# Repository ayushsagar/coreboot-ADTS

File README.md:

coreboot-ADTS
=============

Automated Distributed Test System for coreboot: A Google Summer of Code 2013 project at coreboot.
Original proposal: http://www.google-melange.com/gsoc/project/details/google/gsoc2013/ayush3504/5665319561461760

Please see documentation to see how it is implemented:
https://github.com/ayushsagar/coreboot-ADTS/blob/master/Documentation/test%20interfaces%20for%20CADTS.pdf

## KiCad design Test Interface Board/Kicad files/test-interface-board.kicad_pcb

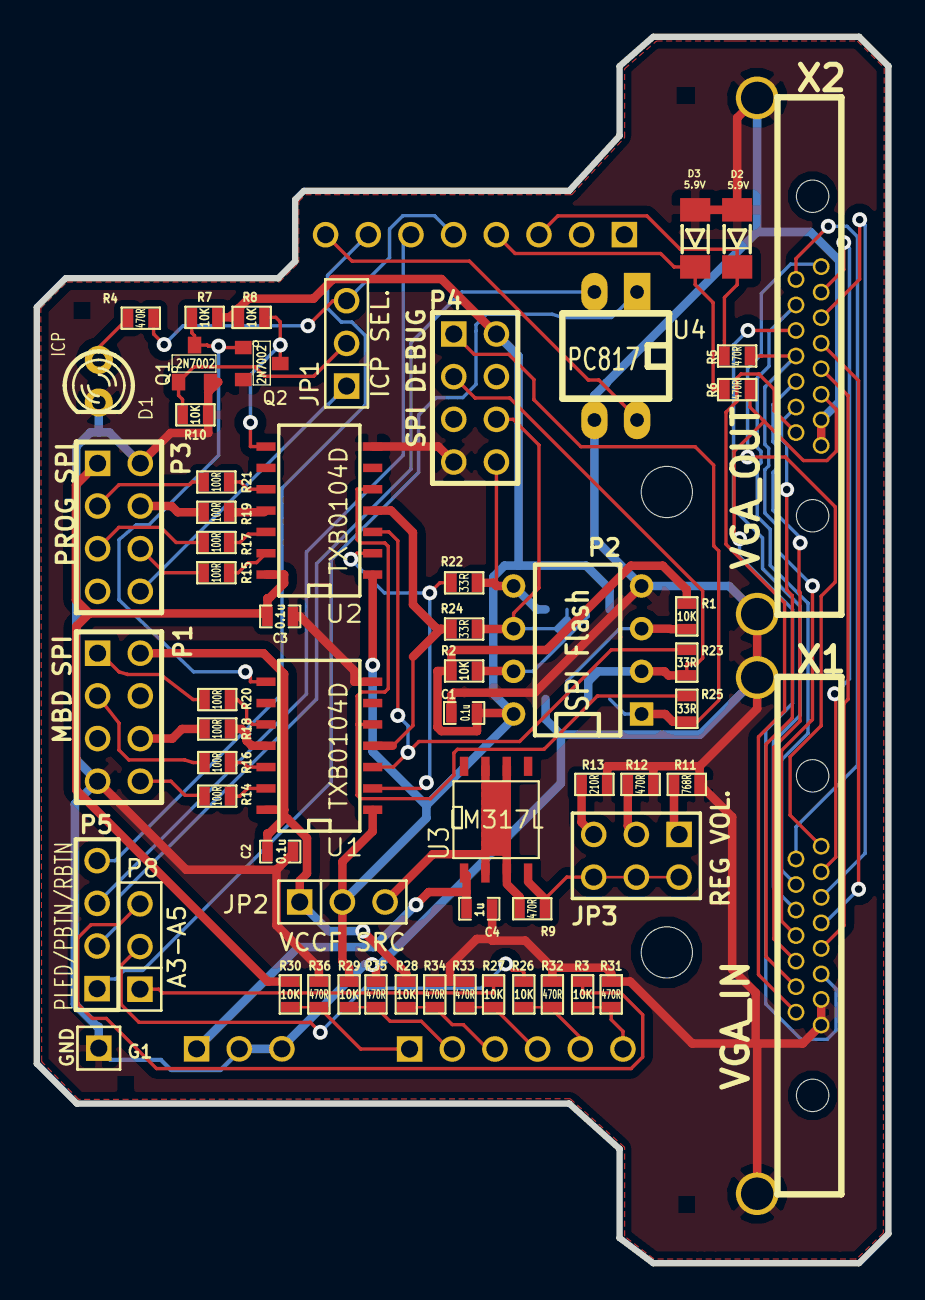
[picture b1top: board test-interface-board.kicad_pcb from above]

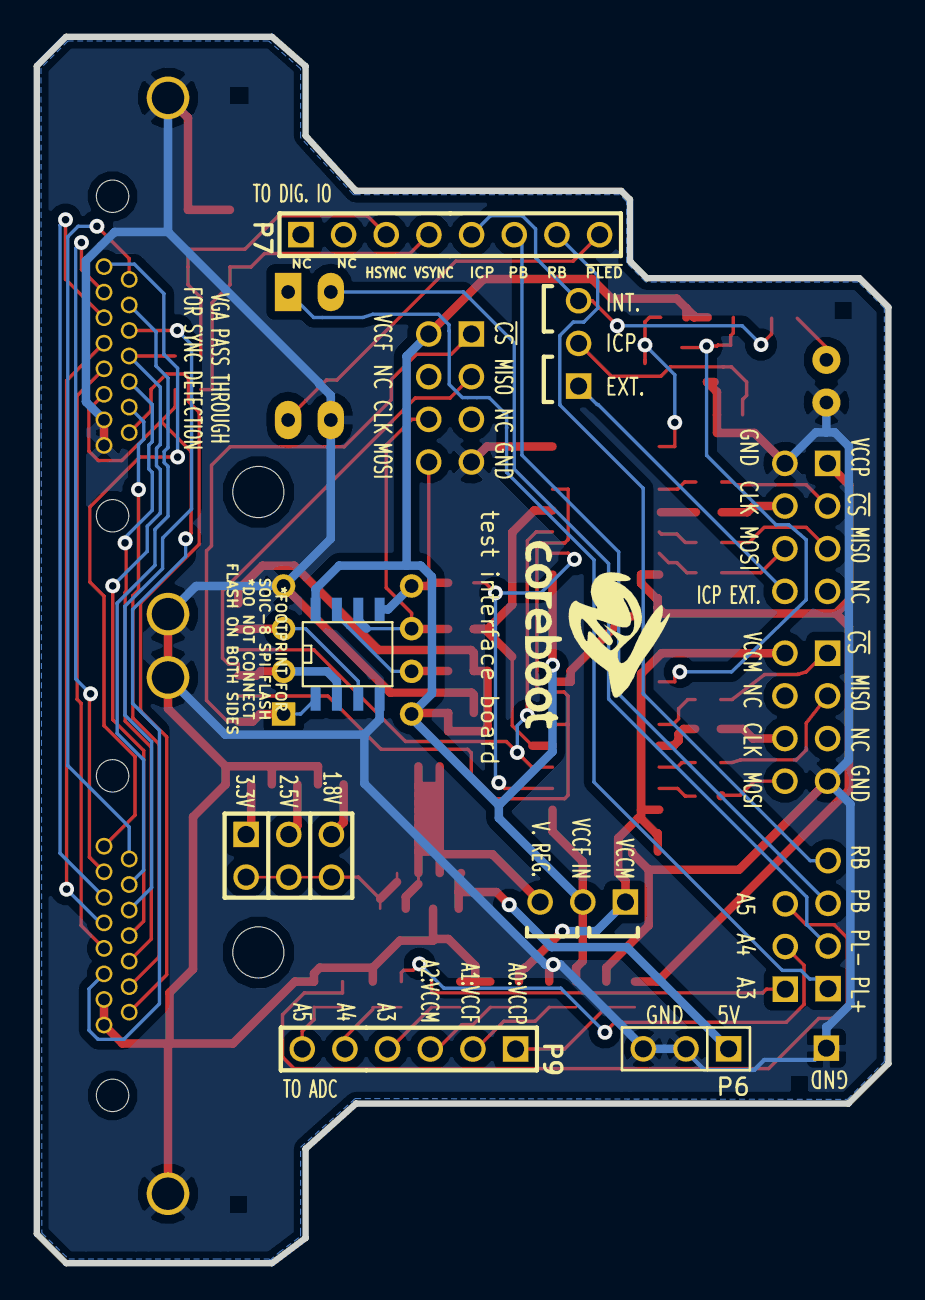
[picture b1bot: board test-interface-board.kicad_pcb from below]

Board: 2 copper layers, 50.7 x 73.0 mm, 67 parts (4 on the bottom side), 71 nets.

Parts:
C1, C2, C3: 0.1u; SM0603_Capa
C4: 1u; SM0603_Capa
D1: ICP; LED-3MM
D2, D3: 5.9V; MiniMelf
G1: GND; PIN_ARRAY_1
JP1: ICP SEL.; PIN_ARRAY_3X1
JP2: VCCF SRC; PIN_ARRAY_3X1
JP3: REG VOL.; pin_array_3x2
P1: MBD SPI; pin_array_4x2
P2: SPI Flash; DIP-8__300
P3: PROG SPI; pin_array_4x2
P4: SPI DEBUG; pin_array_4x2
P5: PLED/PBTN/RBTN; PIN_ARRAY_4x1
P6: POWER; PIN_ARRAY_3X1
P7: D0-D7; PIN_ARRAY_8x1
P8: A3-A5; PIN_ARRAY_3X1
P9: A0-A5; PIN_ARRAY_6x1
P10: SPI Flash; SO8E
Q1, Q2: 2N7002; SOT23
R1, R2, R3, R7, R8, R10, R26, R27, R28, R29, R30: 10K; SM0603
R4, R5, R6, R9, R12, R31, R32, R33, R34, R35, R36: 470R; SM0603
R11: 768R; SM0603
R13: 210R; SM0603
R14, R15, R16, R17, R18, R19, R20, R21: 100R; SM0603
R22, R23, R24, R25: 33R; SM0603
U1, U2: TXB0104D; SO14N
U3: LM317L; SO8N
U4: PC817; DIP-4__300_ELL
V3, V4: 1pin
X1: VGA_IN; EDAC 634-015-274-990 D-Sub High Density 15 pin Slim
X2: VGA_OUT; EDAC 634-015-274-990 D-Sub High Density 15 pin Slim

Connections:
+5V: C4.1, P6.1, U3.1
/HSYNC: D2.2, P7.3, R5.2
/ICP_INT: JP1.3, P7.5, R4.2
/ICP_IO3: JP1.1, P3.8
/PBTN: P5.3, P7.6
/RBTN: P5.4, P7.7
/SPI change-over switch/CLK_F: P2.6, P4.6, P10.6, R24.2
/SPI change-over switch/CLK_M: P1.6, R18.2
/SPI change-over switch/CLK_P: P3.4, R19.2
/SPI change-over switch/ICP: Q2.3, R8.2, U2.8
/SPI change-over switch/MISO_F: P2.2, P4.3, P10.2, R23.2
/SPI change-over switch/MISO_M: P1.3, R16.2
/SPI change-over switch/MISO_P: P3.5, R17.2
/SPI change-over switch/MOSI_F: P2.5, P4.8, P10.5, R22.2
/SPI change-over switch/MOSI_M: P1.8, R14.2
/SPI change-over switch/MOSI_P: P3.6, R15.2
/SPI change-over switch/SET_ICP: JP1.2, Q1.1, R10.1
/SPI change-over switch/~CS_F~: P2.1, P4.1, P10.1, R25.2
/SPI change-over switch/~CS_M~: P1.1, R20.2
/SPI change-over switch/~CS_P~: P3.3, R21.2
/SPI change-over switch/~ICP~: Q1.3, Q2.1, R7.2, U1.8
/VP1: X1.1, X2.1
/VP2: X1.2, X2.2
/VP3: X1.3, X2.3
/VP4: X1.4, X2.4
/VP6: X1.6, X2.6
/VP7: X1.7, X2.7
/VP8: X1.8, X2.8
/VP9: X1.9, X2.9
/VP11: X1.11, X2.11
/VP12: X1.12, X2.12
/VP13: R5.1, X1.13, X2.13
/VP14: R6.1, X1.14, X2.14
/VP15: X1.15, X2.15
/VSYNC: D3.2, P7.4, R6.2
/~HOLD~: P2.7, P10.7, R2.2
/~PLED~: P7.8, U4.4
/~WP~: P2.3, P10.3, R1.2
GND: C1.2, C2.1, C3.1, C4.2, D1.2, D2.1, D3.1, G1.1, P1.7, P2.4, P3.2, P4.7, P6.2, P6.3, P10.4, Q1.2, Q2.2, R10.2, R11.2, R12.2, R13.2, R31.2, R32.2, R33.2, R34.2, R35.2, R36.2, U1.7, U2.7, U4.3, X1.5, X1.10, X1.SH1, X1.SH2, X2.5, X2.10, X2.SH1, X2.SH2
unnamed: P8.1, R27.1
unnamed: P9.4, R27.2, R33.1
unnamed: P9.3, R28.2, R34.1
unnamed: P9.2, R29.2, R35.1
unnamed: P9.1, R30.2, R36.1
unnamed: P8.3, R3.1
unnamed: P8.2, R26.1
unnamed: P9.5, R26.2, R32.1
unnamed: P9.6, R3.2, R31.1
unnamed: P5.2, U4.2
unnamed: P5.1, U4.1
unnamed: D1.1, R4.1
unnamed: JP2.3, R9.2, U3.2, U3.3, U3.6, U3.7
unnamed: JP3.1, R11.1
unnamed: JP3.5, R13.1
unnamed: JP3.3, R12.1
unnamed: R23.1, U1.3, U2.3
unnamed: R22.1, U1.2, U2.2
unnamed: R24.1, U1.4, U2.4
unnamed: R25.1, U1.5, U2.5
unnamed: R20.1, U1.10
unnamed: R17.1, U2.12
unnamed: JP3.2, JP3.4, JP3.6, R9.1, U3.4
unnamed: R15.1, U2.13
unnamed: R19.1, U2.11
unnamed: R21.1, U2.10
unnamed: R14.1, U1.13
unnamed: R16.1, U1.12
unnamed: R18.1, U1.11
VCC_F: C1.1, JP2.2, P2.8, P4.2, P10.8, R1.1, R2.1, R7.1, R8.1, R29.1, U1.1, U2.1
VCC_M: C2.2, JP2.1, P1.2, R28.1, U1.14
VCC_P: C3.2, P3.1, R30.1, U2.14

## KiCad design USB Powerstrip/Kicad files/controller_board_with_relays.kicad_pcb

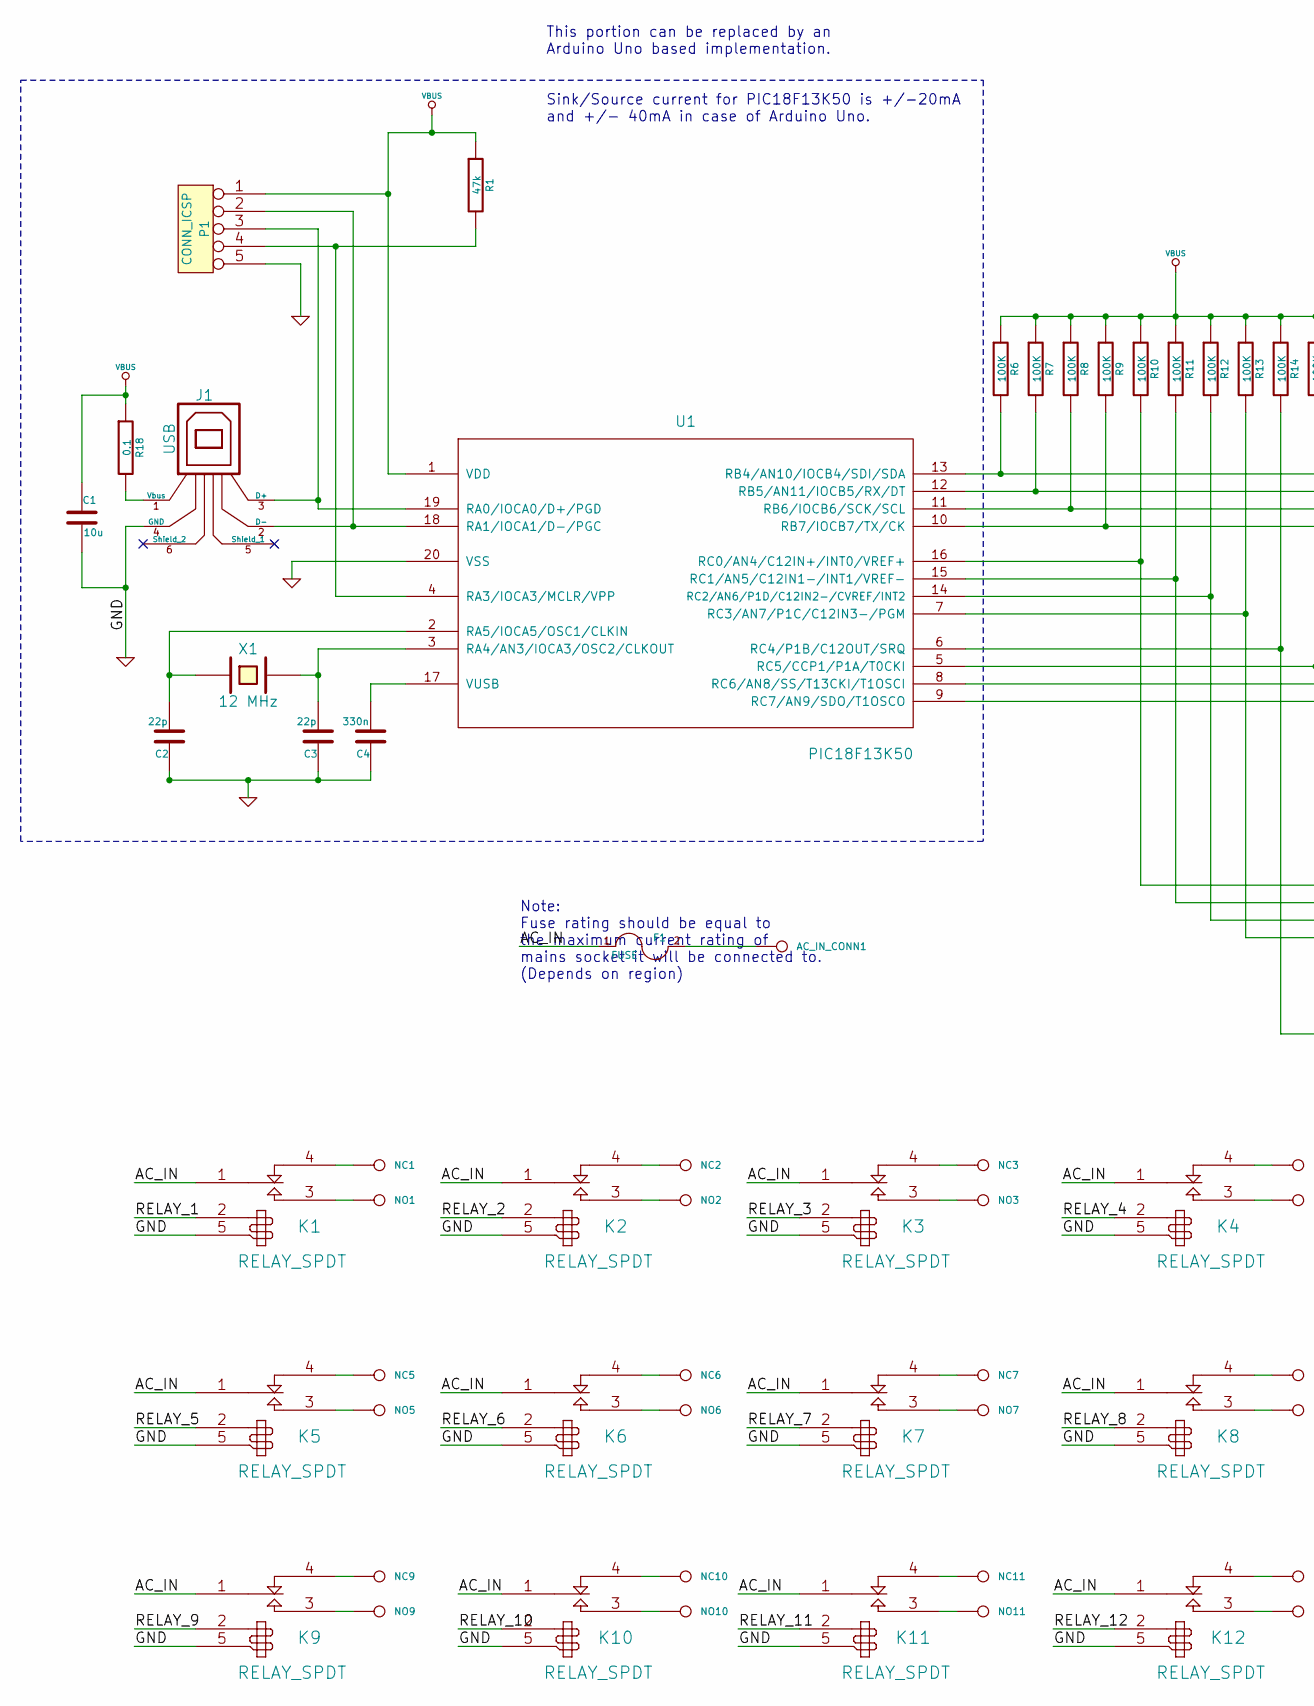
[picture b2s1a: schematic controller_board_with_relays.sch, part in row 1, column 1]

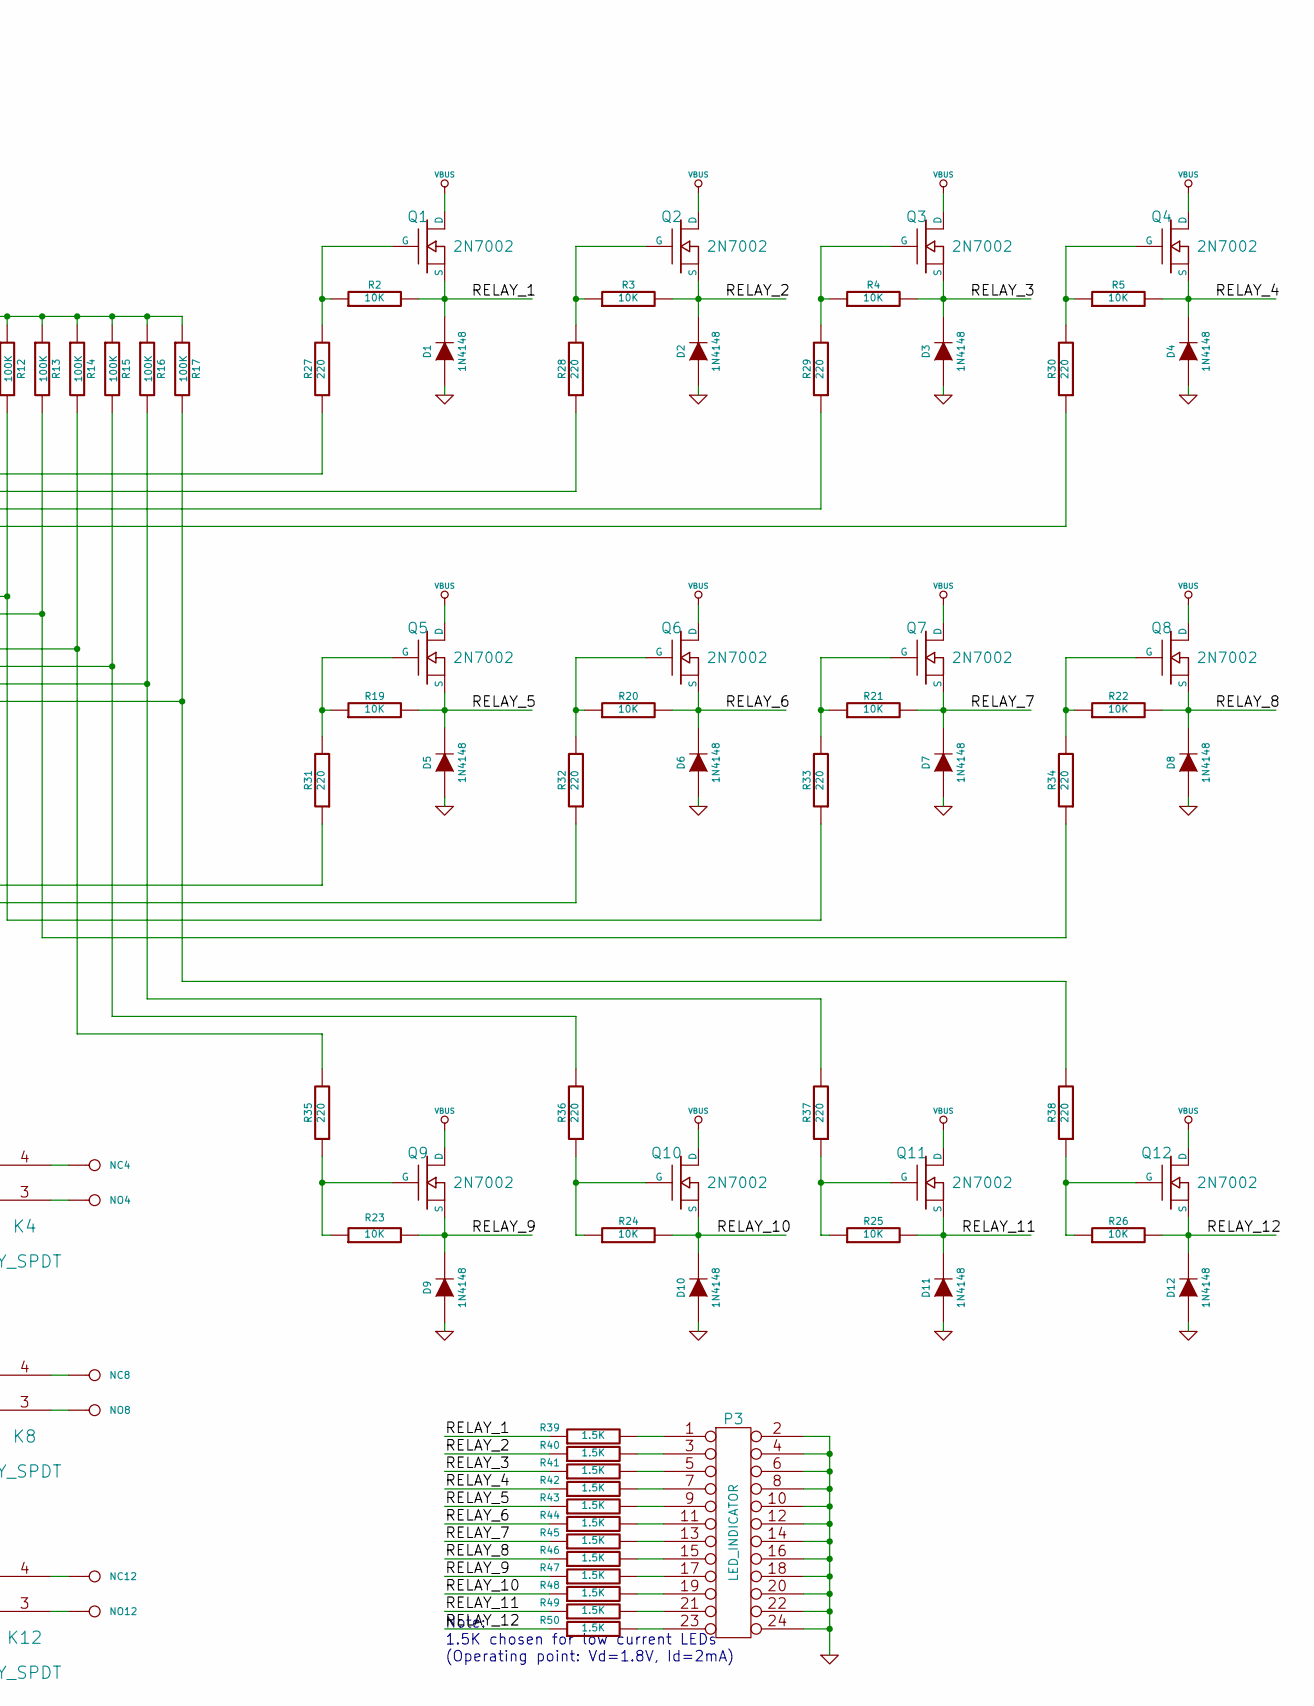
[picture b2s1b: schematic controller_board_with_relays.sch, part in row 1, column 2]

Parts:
AC_IN_CONN1: CONN_1
C1: 10u
C2, C3: 22p
C4: 330n
D1, D2, D3, D4, D5, D6, D7, D8, D9, D10, D11, D12: 1N4148
F1: FUSE
J1: USB
K1, K2, K3, K4, K5, K6, K7, K8, K9, K10, K11, K12: RELAY_SPDT
NC1, NC2, NC3, NC4, NC5, NC6, NC7, NC8, NC9, NC10, NC11, NC12: CONN_1
NO1, NO2, NO3, NO4, NO5, NO6, NO7, NO8, NO9, NO10, NO11, NO12: CONN_1
P1: CONN_ICSP
P3: LED_INDICATOR
Q1, Q2, Q3, Q4, Q5, Q6, Q7, Q8, Q9, Q10, Q11, Q12: 2N7002
R1: 47k
R2, R3, R4, R5, R19, R20, R21, R22, R23, R24, R25, R26: 10K
R6, R7, R8, R9, R10, R11, R12, R13, R14, R15, R16, R17: 100K
R18: 0.1
R27, R28, R29, R30, R31, R32, R33, R34, R35, R36, R37, R38: 220
R39, R40, R41, R42, R43, R44, R45, R46, R47, R48, R49, R50: 1.5K
U1: PIC18F13K50
X1: 12 MHz

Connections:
/AC_IN: F1.1, K1.1 (PWRIN), K2.1 (PWRIN), K3.1 (PWRIN), K4.1 (PWRIN), K5.1 (PWRIN), K6.1 (PWRIN), K7.1 (PWRIN), K8.1 (PWRIN), K9.1 (PWRIN), K10.1 (PWRIN), K11.1 (PWRIN), K12.1 (PWRIN)
/RELAY_1: D1.2 (K), K1.2 (COIL1), Q1.2 (S), R2.2, R39.1
/RELAY_2: D2.2 (K), K2.2 (COIL1), Q2.2 (S), R3.2, R40.1
/RELAY_3: D3.2 (K), K3.2 (COIL1), Q3.2 (S), R4.2, R41.1
/RELAY_4: D4.2 (K), K4.2 (COIL1), Q4.2 (S), R5.2, R42.1
/RELAY_5: D5.2 (K), K5.2 (COIL1), Q5.2 (S), R19.2, R43.1
/RELAY_6: D6.2 (K), K6.2 (COIL1), Q6.2 (S), R20.2, R44.1
/RELAY_7: D7.2 (K), K7.2 (COIL1), Q7.2 (S), R21.2, R45.1
/RELAY_8: D8.2 (K), K8.2 (COIL1), Q8.2 (S), R22.2, R46.1
/RELAY_9: D9.2 (K), K9.2 (COIL1), Q9.2 (S), R23.2, R47.1
/RELAY_10: D10.2 (K), K10.2 (COIL1), Q10.2 (S), R24.2, R48.1
/RELAY_11: D11.2 (K), K11.2 (COIL1), Q11.2 (S), R25.2, R49.1
/RELAY_12: D12.2 (K), K12.2 (COIL1), Q12.2 (S), R26.2, R50.1
GND: C1.2, C2.1, C3.1, C4.1, D1.1 (A), D2.1 (A), D3.1 (A), D4.1 (A), D5.1 (A), D6.1 (A), D7.1 (A), D8.1 (A), D9.1 (A), D10.1 (A), D11.1 (A), D12.1 (A), J1.4 (GND), K1.5 (COIL2), K2.5 (COIL2), K3.5 (COIL2), K4.5 (COIL2), K5.5 (COIL2), K6.5 (COIL2), K7.5 (COIL2), K8.5 (COIL2), K9.5 (COIL2), K10.5 (COIL2), K11.5 (COIL2), K12.5 (COIL2), P1.5, P3.2, P3.4, P3.6, P3.8, P3.10, P3.12, P3.14, P3.16, P3.18, P3.20, P3.22, P3.24, U1.20 (VSS)
unnamed: Q9.1 (G), R23.1, R35.1
unnamed: Q10.1 (G), R24.1, R36.1
unnamed: Q11.1 (G), R25.1, R37.1
unnamed: Q6.1 (G), R20.1, R32.2
unnamed: Q12.1 (G), R26.1, R38.1
unnamed: Q7.1 (G), R21.1, R33.2
unnamed: Q8.1 (G), R22.1, R34.2
unnamed: R13.2, R34.1, U1.7 (RC3/AN7/P1C/C12IN3-/PGM)
unnamed: R14.2, R35.2, U1.6 (RC4/P1B/C12OUT/SRQ)
unnamed: R15.2, R36.2, U1.5 (RC5/CCP1/P1A/T0CKI)
unnamed: R16.2, R37.2, U1.8 (RC6/AN8/SS/T13CKI/T1OSCI)
unnamed: R17.2, R38.2, U1.9 (RC7/AN9/SDO/T1OSCO)
unnamed: R12.2, R33.1, U1.14 (RC2/AN6/P1D/C12IN2-/CVREF/INT2)
unnamed: C3.2, U1.3 (RA4/AN3/IOCA3/OSC2/CLKOUT), X1.2
unnamed: C2.2, U1.2 (RA5/IOCA5/OSC1/CLKIN), X1.1
unnamed: Q1.1 (G), R2.1, R27.2
unnamed: R10.2, R31.1, U1.16 (RC0/AN4/C12IN+/INT0/VREF+)
unnamed: R11.2, R32.1, U1.15 (RC1/AN5/C12IN1-/INT1/VREF-)
unnamed: R6.2, R27.1, U1.13 (RB4/AN10/IOCB4/SDI/SDA)
unnamed: R7.2, R28.1, U1.12 (RB5/AN11/IOCB5/RX/DT)
unnamed: R8.2, R29.1, U1.11 (RB6/IOCB6/SCK/SCL)
unnamed: R9.2, R30.1, U1.10 (RB7/IOCB7/TX/CK)
unnamed: P3.7, R42.2
unnamed: P3.9, R43.2
unnamed: P3.11, R44.2
unnamed: P3.13, R45.2
unnamed: P3.15, R46.2
unnamed: P3.17, R47.2
unnamed: P3.19, R48.2
unnamed: P3.21, R49.2
unnamed: P3.23, R50.2
unnamed: Q2.1 (G), R3.1, R28.2
unnamed: Q3.1 (G), R4.1, R29.2
unnamed: Q4.1 (G), R5.1, R30.2
unnamed: Q5.1 (G), R19.1, R31.2
unnamed: K9.4 (NC), NC9.1
unnamed: K9.3 (NO), NO9.1
unnamed: K10.4 (NC), NC10.1
unnamed: K10.3 (NO), NO10.1
unnamed: K11.4 (NC), NC11.1
unnamed: K7.3 (NO), NO7.1
unnamed: K2.4 (NC), NC2.1
unnamed: K2.3 (NO), NO2.1
unnamed: K3.4 (NC), NC3.1
unnamed: K3.3 (NO), NO3.1
unnamed: K4.4 (NC), NC4.1
unnamed: K4.3 (NO), NO4.1
unnamed: K11.3 (NO), NO11.1
unnamed: K5.4 (NC), NC5.1
unnamed: K5.3 (NO), NO5.1
unnamed: K6.4 (NC), NC6.1
unnamed: K6.3 (NO), NO6.1
unnamed: K7.4 (NC), NC7.1
unnamed: K1.3 (NO), NO1.1
unnamed: K8.4 (NC), NC8.1
unnamed: K8.3 (NO), NO8.1
unnamed: K12.4 (NC), NC12.1
unnamed: K12.3 (NO), NO12.1
unnamed: AC_IN_CONN1.1, F1.2
unnamed: P3.1, R39.2
unnamed: P3.3, R40.2
unnamed: P3.5, R41.2
unnamed: K1.4 (NC), NC1.1
unnamed: J1.2 (D-), P1.2, U1.18 (RA1/IOCA1/D-/PGC)
unnamed: J1.1 (Vbus), R18.2
unnamed: J1.3 (D+), P1.3, U1.19 (RA0/IOCA0/D+/PGD)
unnamed: C4.2, U1.17 (VUSB)
unnamed: P1.4, R1.2, U1.4 (RA3/IOCA3/MCLR/VPP)
VBUS: C1.1, P1.1, Q1.3 (D), Q2.3 (D), Q3.3 (D), Q4.3 (D), Q5.3 (D), Q6.3 (D), Q7.3 (D), Q8.3 (D), Q9.3 (D), Q10.3 (D), Q11.3 (D), Q12.3 (D), R1.1, R6.1, R7.1, R8.1, R9.1, R10.1, R11.1, R12.1, R13.1, R14.1, R15.1, R16.1, R17.1, R18.1, U1.1 (VDD)

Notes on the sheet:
Note: 1.5K chosen for low current LEDs (Operating point: Vd=1.8V, Id=2mA)
Note: Fuse rating should be equal to the maximum current rating of mains socket it will be connected to. (Depends on region)
This portion can be replaced by an Arduino Uno based implementation. Sink/Source current for PIC18F13K50 is +/-20mA and +/- 40mA in case of Arduino Uno.

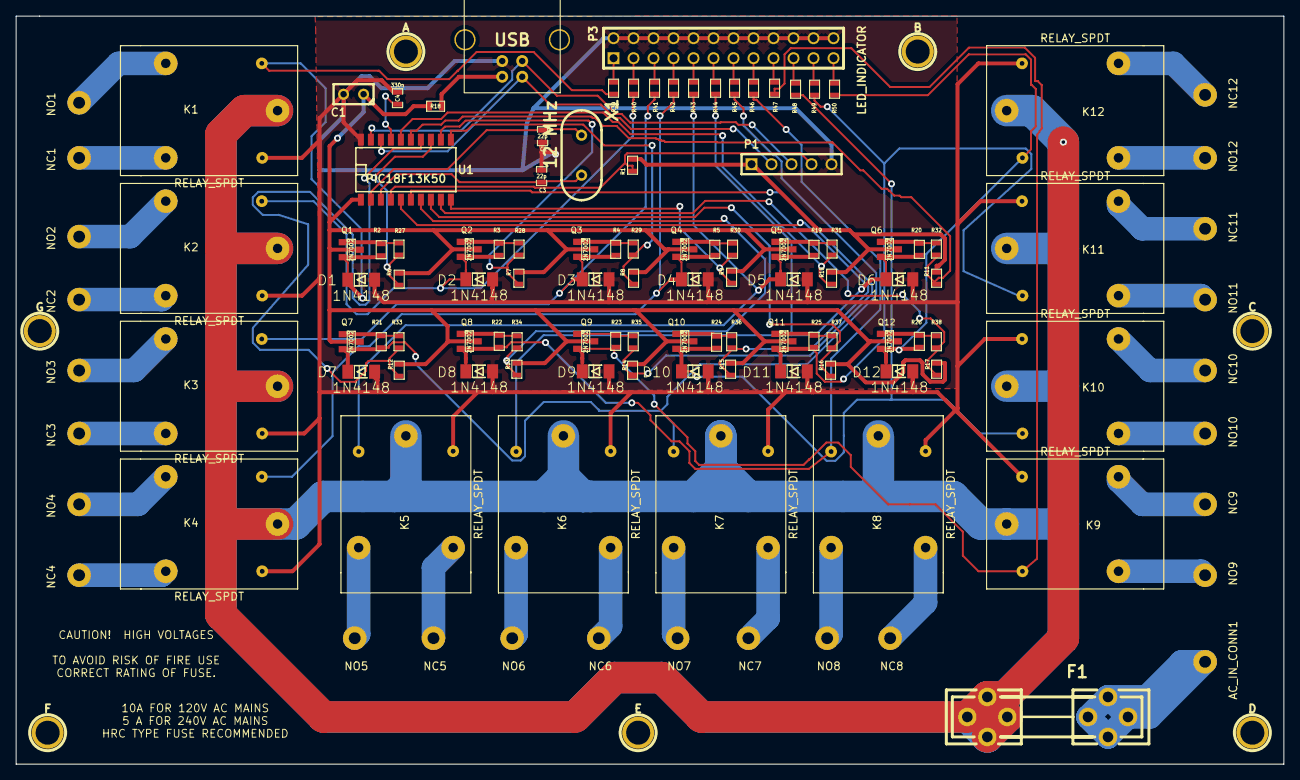
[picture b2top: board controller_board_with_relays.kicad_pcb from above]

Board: 2 copper layers, 161.0 x 95.0 mm, 128 parts (0 on the bottom side), 83 nets.

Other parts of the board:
A: P***; 1pin
B: P***; 1pin
C: P***; 1pin
D: P***; 1pin
E: P***; 1pin
F: P***; 1pin
G: P***; 1pin

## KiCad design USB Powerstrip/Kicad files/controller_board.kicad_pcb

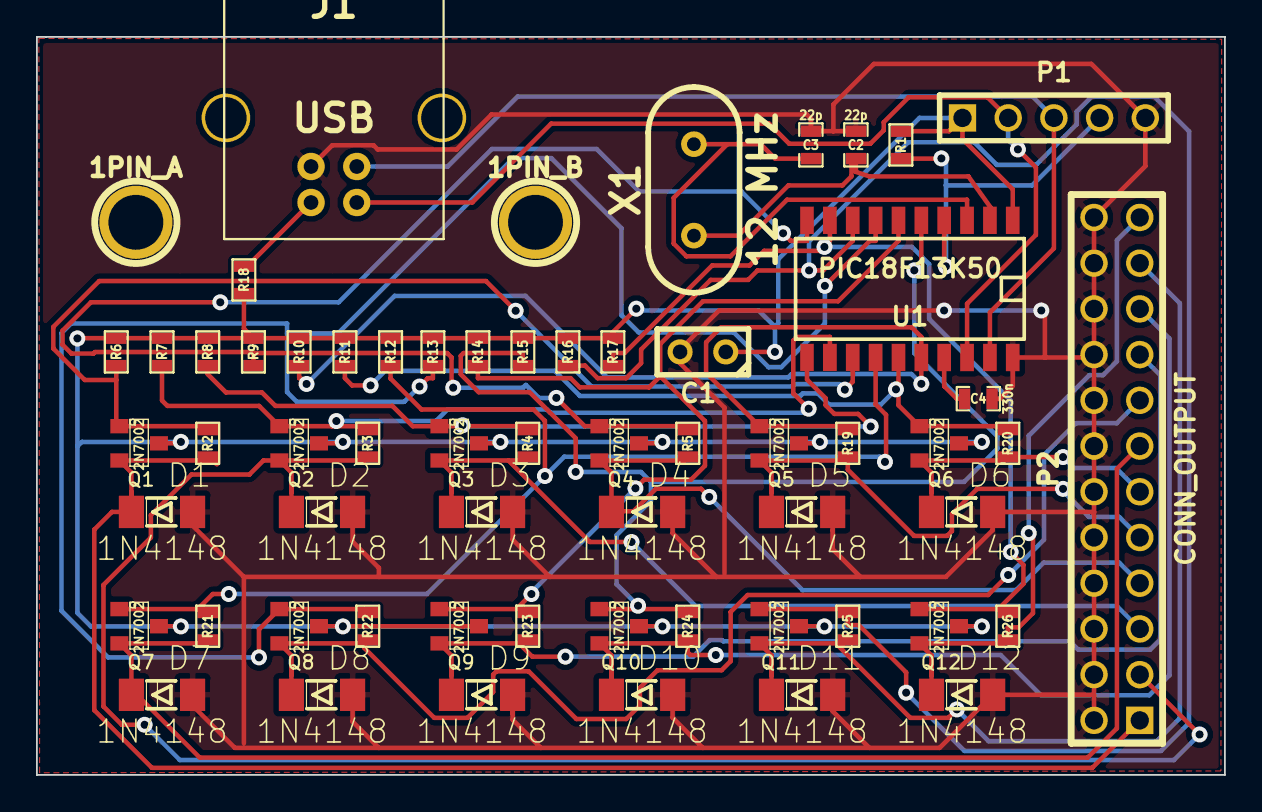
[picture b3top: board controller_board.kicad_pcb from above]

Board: 2 copper layers, 66.0 x 41.0 mm, 61 parts (0 on the bottom side), 33 nets.

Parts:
1PIN_A, 1PIN_B: P***; 1pin
C1: 10u; C1
C2, C3: 22p; SM0603_Capa
C4: 330n; SM0603_Capa
D1, D2, D3, D4, D5, D6, D7, D8, D9, D10, D11, D12: 1N4148; MiniMelf
J1: USB; USB_B
P1: CONN_ICSP; PIN_ARRAY_5x1
P2: CONN_OUTPUT; pin_array_12x2
Q1, Q2, Q3, Q4, Q5, Q6, Q7, Q8, Q9, Q10, Q11, Q12: 2N7002; SOT23
R1: 47k; SM0603
R2, R3, R4, R5, R19, R20, R21, R22, R23, R24, R25, R26: 10K; SM0603
R6, R7, R8, R9, R10, R11, R12, R13, R14, R15, R16, R17: 100K; SM0603
R18: 0.1; SM0603
U1: PIC18F13K50; SOIC20
X1: 12 MHz; HC-49V

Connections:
/RELAY_1: D1.2, P2.1, Q1.2, R2.2
/RELAY_2: D2.2, P2.3, Q2.2, R3.2
/RELAY_3: D3.2, P2.5, Q3.2, R4.2
/RELAY_4: D4.2, P2.7, Q4.2, R5.2
/RELAY_5: D5.2, P2.9, Q5.2, R19.2
/RELAY_6: D6.2, P2.11, Q6.2, R20.2
/RELAY_7: D7.2, P2.13, Q7.2, R21.2
/RELAY_8: D8.2, P2.15, Q8.2, R22.2
/RELAY_9: D9.2, P2.17, Q9.2, R23.2
/RELAY_10: D10.2, P2.19, Q10.2, R24.2
/RELAY_11: D11.2, P2.21, Q11.2, R25.2
/RELAY_12: D12.2, P2.23, Q12.2, R26.2
GND: C1.2, C2.1, C3.1, C4.1, D1.1, D2.1, D3.1, D4.1, D5.1, D6.1, D7.1, D8.1, D9.1, D10.1, D11.1, D12.1, J1.4, P1.5, P2.2, P2.4, P2.6, P2.8, P2.10, P2.12, P2.14, P2.16, P2.18, P2.20, P2.22, P2.24, U1.20
unnamed: J1.2, P1.2, U1.18
unnamed: C3.2, U1.3, X1.2
unnamed: C2.2, U1.2, X1.1
unnamed: Q8.1, R13.2, R22.1, U1.7
unnamed: Q6.1, R11.2, R20.1, U1.15
unnamed: Q7.1, R12.2, R21.1, U1.14
unnamed: Q9.1, R14.2, R23.1, U1.6
unnamed: Q10.1, R15.2, R24.1, U1.5
unnamed: Q11.1, R16.2, R25.1, U1.8
unnamed: Q12.1, R17.2, R26.1, U1.9
unnamed: J1.3, P1.3, U1.19
unnamed: P1.4, R1.2, U1.4
unnamed: J1.1, R18.2
unnamed: C4.2, U1.17
unnamed: Q2.1, R3.1, R7.2, U1.12
unnamed: Q3.1, R4.1, R8.2, U1.11
unnamed: Q5.1, R10.2, R19.1, U1.16
unnamed: Q4.1, R5.1, R9.2, U1.10
unnamed: Q1.1, R2.1, R6.2, U1.13
VBUS: C1.1, P1.1, Q1.3, Q2.3, Q3.3, Q4.3, Q5.3, Q6.3, Q7.3, Q8.3, Q9.3, Q10.3, Q11.3, Q12.3, R1.1, R6.1, R7.1, R8.1, R9.1, R10.1, R11.1, R12.1, R13.1, R14.1, R15.1, R16.1, R17.1, R18.1, U1.1

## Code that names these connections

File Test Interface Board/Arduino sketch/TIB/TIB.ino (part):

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#define pinVCCF A1
#define pinVCCM A2

// Note: HSync and VSync pins are assigned to pins 2 and 3 using attachInterrupt() in beginFreqCounter()


//     ADC related
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volatile unsigned long VSPulseCount = 0;

  // stores HSync and VSync frequency in Hz
unsigned long HSync = 0;
unsigned long VSync = 0;

  // sets timer limit in msec for HSync and VSync frequency counter
#define fcTimerLimit 500
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  // start serial at 9600 bps, 8 bits, no parity, 1 stop bit
  Serial.begin(9600);
  
  // set pin modes for ICP and power LED pins.
  pinMode(pinICP, OUTPUT);
  pinMode(pinPowerLED, INPUT_PULLUP);  //internal pull-up is required to translate open-drain output of PWR_LED signal source.
  
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  VSPulseCount = 0;

  // enable frequency counter interrupts
  attachInterrupt(0, incrementHSPulseCount, FALLING); // falling edge on pin 2 calls increment function for HSync counter
  attachInterrupt(1, incrementVSPulseCount, FALLING); // falling edge on pin 3 calls increment function for VSync counter
  
  // convey to loop() that counter is active
  flagCounterActive = true;
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
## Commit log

2013-10-30 Documentation v.1.0 published

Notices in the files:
Test Interface Board/Arduino sketch/TIB/TIB.ino:
Copyright (C) 2013 Ayush Sagar <ayush@ieee.org>
This program is free software; you can redistribute it and/or modify
it under the terms of the GNU General Public License as published by
the Free Software Foundation; either version 2 of the License, or
(at your option) any later version.
